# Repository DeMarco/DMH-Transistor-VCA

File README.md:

# DMH-Transistor-VCA
Classic transistor based VCA module design

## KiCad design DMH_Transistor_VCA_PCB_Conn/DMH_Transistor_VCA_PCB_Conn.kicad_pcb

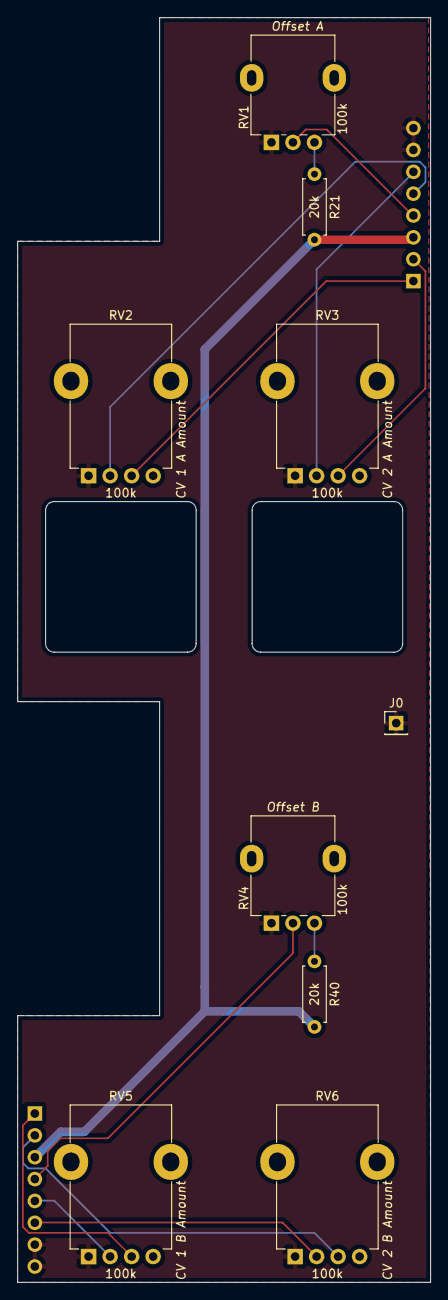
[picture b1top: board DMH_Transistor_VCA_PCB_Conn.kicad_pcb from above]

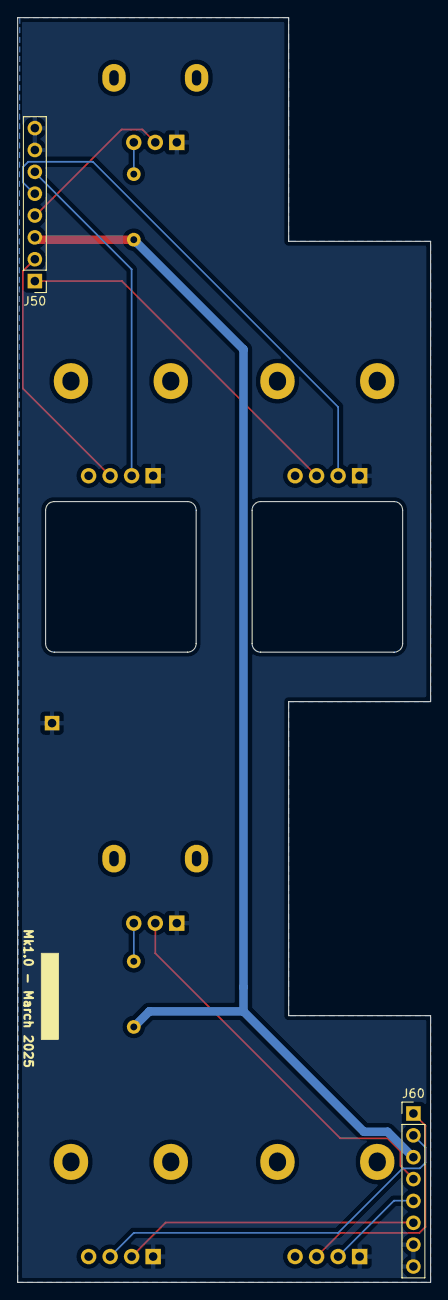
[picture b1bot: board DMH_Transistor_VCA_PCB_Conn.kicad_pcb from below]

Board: 2 copper layers, 48.0 x 147.0 mm, 11 parts (2 on the bottom side), 14 nets.

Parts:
J0: Conn_01x01; PinHeader_1x01_P2.54mm_Vertical
J50, J60: Conn_01x08; PinHeader_1x08_P2.54mm_Vertical
R21, R40: 20k; R_Axial_DIN0207_L6.3mm_D2.5mm_P7.62mm_Horizontal
RV1, RV4: 100k; Potentiometer_Alpha_RD901F-40-00D_Single_Vertical
RV2, RV3, RV5, RV6: 100k; Potentiometer_TT_P110KH1

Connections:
+12V: J50.3, J60.3, R21.2, R40.2
/Inputs and Outputs/CV 1 A Jack: J50.1, RV2.3
/Inputs and Outputs/CV 1 A Pot: J50.5, RV2.2
/Inputs and Outputs/CV 1 B Jack: J60.1, RV5.3
/Inputs and Outputs/CV 1 B Pot: J60.5, RV5.2
/Inputs and Outputs/CV 2 A Jack: J50.2, RV3.3
/Inputs and Outputs/CV 2 A Pot: J50.6, RV3.2
/Inputs and Outputs/CV 2 B Jack: J60.2, RV6.3
/Inputs and Outputs/CV 2 B Pot: J60.6, RV6.2
/Inputs and Outputs/Offset A Pot: J50.4, RV1.2
/Inputs and Outputs/Offset B Pot: J60.4, RV4.2
GND: J0.1, J50.7, J50.8, J60.7, J60.8, RV1.1, RV2.1, RV3.1, RV4.1, RV5.1, RV6.1
unnamed: R21.1, RV1.3
unnamed: R40.1, RV4.3

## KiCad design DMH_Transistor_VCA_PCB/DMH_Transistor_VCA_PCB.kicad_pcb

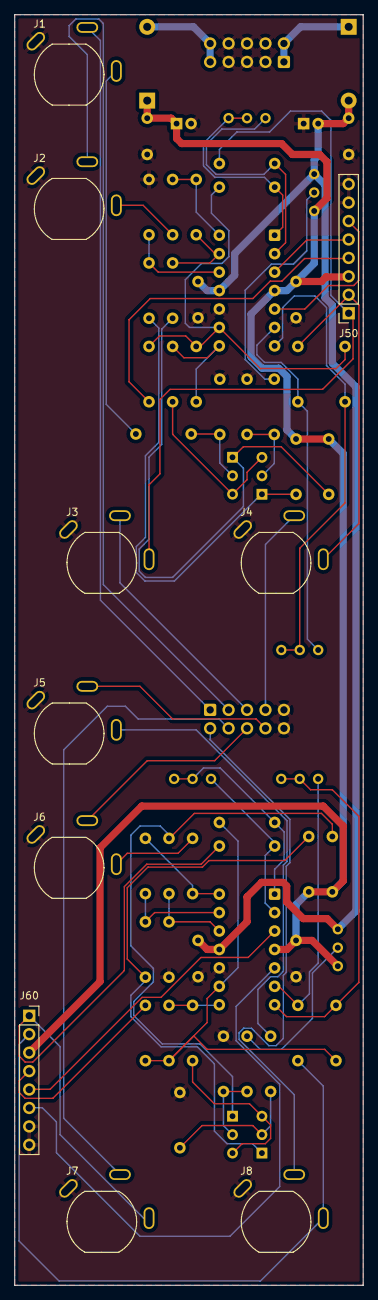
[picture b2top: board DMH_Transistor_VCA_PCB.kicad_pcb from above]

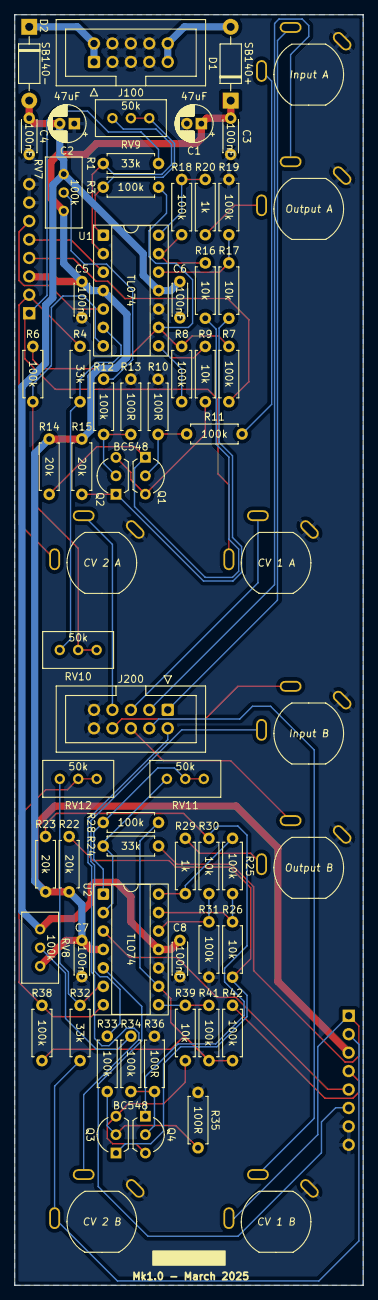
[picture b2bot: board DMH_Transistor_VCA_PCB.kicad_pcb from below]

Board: 2 copper layers, 48.0 x 175.0 mm, 70 parts (60 on the bottom side), 57 nets.

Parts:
C1, C2: 47uF; CP_Radial_D5.0mm_P2.00mm
C3, C4, C5, C6, C7, C8: 100nF; C_Disc_D4.3mm_W1.9mm_P5.00mm
D1: SB140+; D_DO-41_SOD81_P10.16mm_Horizontal
D2: SB140-; D_DO-41_SOD81_P10.16mm_Horizontal
J1, J2, J3, J4, J5, J6, J7, J8: TS_Jack_6.35mm_Sw; CUI_MJ-63052A
J50, J60: Conn_01x08; PinSocket_1x08_P2.54mm_Vertical
J100: IDC_02x05; IDC-Header_2x05_P2.54mm_Vertical_Eurorack
J200: IDC_02x05; IDC-Header_2x05_P2.54mm_Vertical_BackBone
Q1, Q2, Q3, Q4: BC548; TO-92L_Inline_Wide
R1, R4, R24, R32: 33k; R_Axial_DIN0207_L6.3mm_D2.5mm_P7.62mm_Horizontal
R3, R6, R7, R8, R11, R12, R18, R19, R25, R28, R31, R33, R34, R38, R41, R42: 100k; R_Axial_DIN0207_L6.3mm_D2.5mm_P7.62mm_Horizontal
R9, R16, R17, R26, R30, R39: 10k; R_Axial_DIN0207_L6.3mm_D2.5mm_P7.62mm_Horizontal
R10, R13, R35, R36: 100R; R_Axial_DIN0207_L6.3mm_D2.5mm_P7.62mm_Horizontal
R14, R15, R22, R23: 20k; R_Axial_DIN0207_L6.3mm_D2.5mm_P7.62mm_Horizontal
R20, R29: 1k; R_Axial_DIN0207_L6.3mm_D2.5mm_P7.62mm_Horizontal
RV7, RV8: 100k; Potentiometer_Bourns_3296W_Vertical
RV9, RV10, RV11, RV12: 50k; Potentiometer_Bourns_3296W_Vertical
U1, U2: TL074; DIP-14_W7.62mm_Socket

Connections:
+12V: C1.1, C3.1, C5.1, C7.1, D1.1 (K), J50.3, J60.3, R14.2, R15.2, R22.2, R23.2, RV7.3, RV8.3, U1.4 (V+), U2.4 (V+)
-12V: C2.2, C4.2, C6.2, C8.2, D2.2 (A), RV7.1, RV8.1, U1.11 (V-), U2.11 (V-)
/Core Circuit A/CV 1 A Input: J3.T, J50.1, R1.1
/Core Circuit A/CV 1 A Pot: J50.5, U1.3 (+)
/Core Circuit A/CV 2 A Input: J4.T, J50.2, R4.1
/Core Circuit A/CV 2 A Pot: J50.6, U1.5 (+)
/Core Circuit A/Input A: J1.T, R11.2
/Core Circuit A/Offset A Pot: J50.4, R7.1
/Core Circuit A/Output A: J2.T, R20.1
/Core Circuit B/CV 1 B Input: J7.T, J60.1, R24.1
/Core Circuit B/CV 1 B Pot: J60.5, U2.3 (+)
/Core Circuit B/CV 2 B Input: J8.T, J60.2, R32.1
/Core Circuit B/CV 2 B Pot: J60.6, U2.5 (+)
/Core Circuit B/Input B: J5.T, R33.2
/Core Circuit B/Offset B Pot: J60.4, R42.1
/Core Circuit B/Output B: J6.T, R29.1
GND: C1.2, C2.1, C3.2, C4.1, C5.2, C6.1, C7.2, C8.1, J1.S, J2.S, J3.S, J4.S, J5.S, J6.S, J7.S, J8.S, J50.7, J50.8, J60.7, J60.8, J100.2a, J100.2b, J100.3a, J100.3b, J100.4a, J100.4b, J200.5, J200.10, R10.1, R13.1, R19.2, R31.2, R35.1, R36.1, U1.10 (+), U2.10 (+)
unnamed: D1.2 (A), J100.5a, J100.5b
unnamed: D2.1 (K), J100.1a, J100.1b
unnamed: J1.TN, J200.1
unnamed: J2.TN, J200.2
unnamed: J3.TN, J200.3
unnamed: J4.TN, J200.4
unnamed: J8.TN, J200.6
unnamed: J7.TN, J200.7
unnamed: J6.TN, J200.8
unnamed: J5.TN, J200.9
unnamed: Q1.2 (B), R10.2, R11.1
unnamed: Q1.1 (C), R14.1, R16.2
unnamed: Q1.3 (E), Q2.3 (E), R9.2
unnamed: Q2.2 (B), R12.2, R13.2
unnamed: Q2.1 (C), R15.1, R17.2
unnamed: Q3.2 (B), R33.1, R35.2
unnamed: Q3.1 (C), R22.1, R26.2
unnamed: Q3.3 (E), Q4.3 (E), R39.2
unnamed: Q4.2 (B), R34.2, R36.2
unnamed: Q4.1 (C), R23.1, R30.2
unnamed: R3.1, RV9.2, RV9.3, U1.1
unnamed: R6.1, RV10.2, RV10.3, U1.7
unnamed: R8.2, R9.1, U1.8
unnamed: R12.1, RV7.2
unnamed: R18.1, R20.2, U1.14
unnamed: R25.1, R29.2, U2.14
unnamed: R28.1, RV11.2, RV11.3, U2.1
unnamed: R34.1, RV8.2
unnamed: R38.1, RV12.2, RV12.3, U2.7
unnamed: R39.1, R41.2, U2.8
unnamed: R1.2, RV9.1, U1.2 (-)
unnamed: R4.2, RV10.1, U1.6 (-)
unnamed: R3.2, R6.2, R7.2, R8.1, U1.9 (-)
unnamed: R17.1, R19.1, U1.12 (+)
unnamed: R16.1, R18.2, U1.13 (-)
unnamed: R24.2, RV11.1, U2.2 (-)
unnamed: R32.2, RV12.1, U2.6 (-)
unnamed: R28.2, R38.2, R41.1, R42.2, U2.9 (-)
unnamed: R30.1, R31.1, U2.12 (+)
unnamed: R25.2, R26.1, U2.13 (-)

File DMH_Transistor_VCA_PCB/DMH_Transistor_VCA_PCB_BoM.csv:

"Reference","Value","Footprint","Qty","DNP"
"C1,C2","47uF","Capacitor_THT:CP_Radial_D5.0mm_P2.00mm","2",""
"C3,C4,C5,C6,C7,C8","100nF","Capacitor_THT:C_Disc_D4.3mm_W1.9mm_P5.00mm","6",""
"D1","SB140+","Diode_THT:D_DO-41_SOD81_P10.16mm_Horizontal","1",""
"D2","SB140-","Diode_THT:D_DO-41_SOD81_P10.16mm_Horizontal","1",""
"J0","Conn_01x01","Connector_PinHeader_2.54mm:PinHeader_1x01_P2.54mm_Vertical","1",""
"J1,J2,J3,J4,J5,J6,J7,J8","TS_Jack_6.35mm_Sw","SynthStuff:CUI_MJ-63052A","8",""
"J50,J60","Conn_01x08","Connector_PinSocket_2.54mm:PinSocket_1x08_P2.54mm_Vertical","2",""
"J100","IDC_02x05","SynthStuff:IDC-Header_2x05_P2.54mm_Vertical_Eurorack","1",""
"J200","IDC_02x05","SynthStuff:IDC-Header_2x05_P2.54mm_Vertical_BackBone","1",""
"Q1,Q2,Q3,Q4","BC548","Package_TO_SOT_THT:TO-92L_Inline_Wide","4",""
"R1,R2,R3,R4,R5,R6,R7,R11,R12,R18,R19,R24,R25,R27,R28,R31,R32,R33,R34,R37,R38,R42","100k","Resistor_THT:R_Axial_DIN0207_L6.3mm_D2.5mm_P7.62mm_Horizontal","22",""
"R8,R41","82k","Resistor_THT:R_Axial_DIN0207_L6.3mm_D2.5mm_P7.62mm_Horizontal","2",""
"R9,R16,R17,R26,R30,R39","10k","Resistor_THT:R_Axial_DIN0207_L6.3mm_D2.5mm_P7.62mm_Horizontal","6",""
"R10,R13,R35,R36","100R","Resistor_THT:R_Axial_DIN0207_L6.3mm_D2.5mm_P7.62mm_Horizontal","4",""
"R14,R15,R21,R22,R23,R40","20k","Resistor_THT:R_Axial_DIN0207_L6.3mm_D2.5mm_P7.62mm_Horizontal","6",""
"R20,R29","1k","Resistor_THT:R_Axial_DIN0207_L6.3mm_D2.5mm_P7.62mm_Horizontal","2",""
"RV1,RV4","100k","SynthStuff:Potentiometer_Alpha_RD901F-40-00D_Single_Vertical","2",""
"RV2,RV3,RV5,RV6","100k","SynthStuff:Potentiometer_TT_P110KH1","4",""
"RV7,RV8","100k","Potentiometer_THT:Potentiometer_Bourns_3296W_Vertical","2",""
"U1,U2","TL074","Package_DIP:DIP-14_W7.62mm_Socket","2",""
"U2","TL074","","1",""

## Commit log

2024-11-30 Created KiCad projects
2024-11-30 Started panel design
2024-11-30 Panel design ongoing
2024-12-01 Front panel ongoing
2024-12-01 Front panel design ongoing
2024-12-04 Panel experiment in progress
2024-12-04 Went back to panel original idea
2024-12-04 Finished core circuit schematic
2024-12-07 Finished schematic
2024-12-07 Finished main PCB
2024-12-08 Pots PCB in progress
    Need to add CV input traces to the pin headers
2024-12-08 Finished Pots PCB
2024-12-08 Exported BoM
2024-12-09 VCM studies
2024-12-27 sync libs
2024-12-29 Added CV input attenuverter adjustment trimpots
2024-12-29 Perfected pots (_conn) PCB
2024-12-31 Switched attenuverters trimpot and Rf positions
2025-02-23 Converted to Kicad 9
2025-02-23 Changed R8 and R41 to 100k
    ... in order to remove gain reduction of the incoming CV and offset
2025-03-16 Generated Gerbers
